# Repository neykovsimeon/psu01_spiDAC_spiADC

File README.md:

# PIC18F2525 with with character 20x4 LCD display

----
## Linear Lab Power Suuply project on PIC18F2525
> IDE MPLAB X IDE 5.05
> Compiler XC8 v2.00

> Use of legacy Microchip's peripheral libraries "plib"  with remarks:

- as for LCD -> changed ports assignments, means the libraries have to be re-located as follows:
  - header file "xlcd.h" moved and included as a local project's  header files, modified respectively
  - source files moved and included as a local project's files , so they are being recompiled

- plib concept used also for spi communications 
  - My git repo for plib archive (while I was still able to find them on Microchip's website):
[plib](https://github.com/neykovsimeon/pic18_plib_legacy.git) 

 - Very helpful "Getting started" tutorial for MPLAB X IDE and XC8:
 [Refrence - YouTube channel StudentCompanion](https://www.youtube.com/watch?v=mUofSucHx_E&list=PL3lfkED2i6JcJH-OETxsI43e8M-7eLeL-)

> use of Universal Programmer MiniPro TL866A. Fuses config comes directly with hex file as per #pragma config statements in respective header file

----
## Scope of this Project
1. Create a bunch of re-usable C functions to utilize 20x4 character display and menu interface
 - [Reference - YouTube channel projectsHigaski, LCD menu tutorial for microcontrollers](https://www.youtube.com/watch?v=PFzNBtnfJ6Y&list=PLfGDzGG5F5eYNBkXs0tTdXqLB3KE5CFgx)
 
2. Use of Microchip's 12bit spi DAC MCP4921 as a set output voltage command interface for the unit

3. Use of Microchip's 12bit spi ADC MCP3208 as for output Voltmener and  Ampermeter

4. Dedicated and re-usable menu structure, easy to handle:
 - menu item selector
 - events handlers ("up", "down", "enter") based on pushbuttons or / and rotary encoder with switch
 - specified function might be called by any of the events handlers (but it is considered event "enter" is the logical way of use)

5. As for fun-trial -> control LCD display's contrast and lightenning via digital potentiometer MCP42010 and PWM on a timer 555
 - [Reference - YouTube EEVblog #392](https://www.youtube.com/watch?v=OXsu29K_Ap4&t=943s)

6. Tracking pre-regulator based on LM2576T-ADJ. Note MCU has no function on this part.
 - [Reference - YouTube EEVblog #260](https://www.youtube.com/watch?v=iTxKCQYMHbY)

7. Output voltage range: 0-15V, (supposed to be 6* Vset, Vset is DAC command voltage at 2.5V Reference voltage with TL431)

8. Output current limit/protection functionality, low side current sense concept used, max current possible (from firmware perspective, in terms of the DAC range) 2.5A.
 - Actual max current would depends of the output power transistors used, heat-sink applied, and the capability of the input voltage source.
   - In my trials I used an laptop power adapter, 20V, 3A.  
   
9. Added  spi serial to parallel I/O expander MCP23S08 together with I/O buffer UDN2595 for higher sink current capability
 - used as an output expander in this project
 - used to control relays and LEDs respectively
 - relays used in a perspective to introduce:
   - PSU output ON/OFF (connect / disconnect) functionality
   - PSU output configured in 2 wire or 4 wite (force / sense concept)
 - added functions 'relDriver_memSet()' , 'relDriver_relSet()'
 - disregarded pushbuttons functionality linked to menu browsing and implemented pushbuttons functions to drive relays respectively
 - 2-wire/4-wire switching not allowed when output is connected (ON)
 - if output change from OFF to ON while 4 wire config - display warning message to make physical connections - wait to press OK to continue!

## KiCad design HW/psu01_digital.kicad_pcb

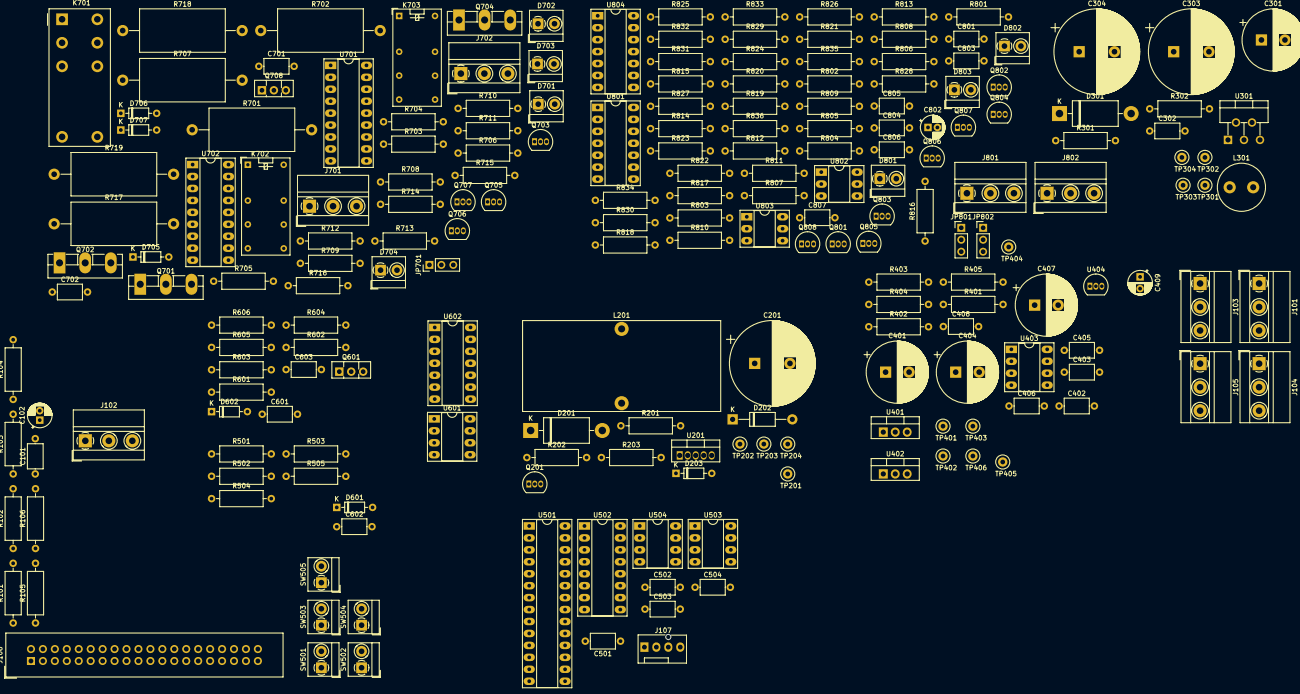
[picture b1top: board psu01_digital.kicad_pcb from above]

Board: 2 copper layers, 204 parts (0 on the bottom side), 139 nets, no tracks yet.

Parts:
C101, C302, C402, C403, C405, C406, C408, C501, C502, C503, C504, C601, C602, C701, C702, C801, C803, C805, C807: 100n; C_Axial_L5.1mm_D3.1mm_P7.50mm_Horizontal
C102: 1uF; CP_Radial_D5.0mm_P2.00mm
C201: 1000uF/63V; CP_Radial_D18.0mm_P7.50mm
C301, C401, C404, C407: 470uF; CP_Radial_D13.0mm_P5.00mm
C303, C304: 2200uF; CP_Radial_D18.0mm_P7.50mm
C409: 1uF; CP_Radial_D5.0mm_P2.50mm
C603: 10n; C_Axial_L5.1mm_D3.1mm_P7.50mm_Horizontal
C802: 10uF; CP_Radial_D5.0mm_P2.00mm
C804, C806: 2.2n; C_Axial_L5.1mm_D3.1mm_P7.50mm_Horizontal
D201, D301: 1N5822; D_DO-201AD_P15.24mm_Horizontal
D202: BZX85C2V7; D_DO-41_SOD81_P12.70mm_Horizontal
D203, D601, D602, D705, D706, D707: 1N4148; D_DO-35_SOD27_P7.62mm_Horizontal
D701, D702: 4wire; TerminalBlock_MetzConnect_Type059_RT06302HBWC_1x02_P3.50mm_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
D703: 2wire; TerminalBlock_MetzConnect_Type059_RT06302HBWC_1x02_P3.50mm_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
D704: Out_OnOff; TerminalBlock_MetzConnect_Type059_RT06302HBWC_1x02_P3.50mm_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
D801: V_REG; TerminalBlock_MetzConnect_Type059_RT06302HBWC_1x02_P3.50mm_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
D802: ALARM; TerminalBlock_MetzConnect_Type059_RT06302HBWC_1x02_P3.50mm_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
D803: I_REG; TerminalBlock_MetzConnect_Type059_RT06302HBWC_1x02_P3.50mm_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
J101: Analog Amper; TerminalBlock_MetzConnect_Type011_RT05503HBWC_1x03_P5.00mm_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
J102: Input_19V; TerminalBlock_MetzConnect_Type011_RT05503HBWC_1x03_P5.00mm_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
J103: FS+; TerminalBlock_MetzConnect_Type011_RT05503HBWC_1x03_P5.00mm_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
J104: Analog Volt; TerminalBlock_MetzConnect_Type011_RT05503HBWC_1x03_P5.00mm_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
J105: FS-; TerminalBlock_MetzConnect_Type011_RT05503HBWC_1x03_P5.00mm_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
J106: ui_iterface; IDC-Header_2x20_P2.54mm_Vertical
J107: BB-CH340T; FanPinHeader_1x04_P2.54mm_Vertical
J701, J702: Screw_Terminal_01x03; TerminalBlock_MetzConnect_Type011_RT05503HBWC_1x03_P5.00mm_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
J801: U_POT_option; TerminalBlock_MetzConnect_Type011_RT05503HBWC_1x03_P5.00mm_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
J802: I_POT_option; TerminalBlock_MetzConnect_Type011_RT05503HBWC_1x03_P5.00mm_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
JP701: Sel_Force_Sense; PinHeader_1x03_P2.54mm_Vertical
JP801: U_POT_option; PinHeader_1x03_P2.54mm_Vertical
JP802: I_POT_option; PinHeader_1x03_P2.54mm_Vertical
K701: Omron_G2RL-2-5VDC; Relay_DPDT_Fujitsu_FTR-F1C
K702, K703: Fujutsu_RY5W-K; Relay_DPDT_Omron_G5V-2
L201: CL100uH_RBQE; L_Toroid_Vertical_L41.9mm_W19.1mm_P15.80mm_Vishay_TJ7
L301: CL33uH_CW8A; L_Radial_D10.0mm_P5.00mm_Fastron_07M
Q201, Q705, Q706: BC557; TO-92_Inline
Q601: BD140; TO-126-3_Vertical
Q701, Q702, Q704: 2SD1047; TO-3PB-3_Vertical
Q703, Q707: BC546; TO-92_Inline
Q708: BD139; TO-126-3_Vertical
Q801, Q802, Q803, Q804, Q805, Q806, Q807, Q808: BC547; TO-92_Inline
R101, R102, R103, R201, R202, R401, R403, R404, R405, R501, R502, R503, R504, R505, R706, R801, R802, R803, R805, R806, R807, R811, R812, R816, R817, R818, R819, R820, R821, R822, R824, R825, R826, R827, R829, R830, R833, R834, R836: 10k; R_Axial_DIN0309_L9.0mm_D3.2mm_P12.70mm_Horizontal
R104, R105, R106: 1meg; R_Axial_DIN0309_L9.0mm_D3.2mm_P12.70mm_Horizontal
R203: 890; R_Axial_DIN0309_L9.0mm_D3.2mm_P12.70mm_Horizontal
R301: 3.2k; R_Axial_DIN0309_L9.0mm_D3.2mm_P12.70mm_Horizontal
R302: 39k; R_Axial_DIN0309_L9.0mm_D3.2mm_P12.70mm_Horizontal
R402, R708, R710: 270; R_Axial_DIN0309_L9.0mm_D3.2mm_P12.70mm_Horizontal
R601: 120k; R_Axial_DIN0309_L9.0mm_D3.2mm_P12.70mm_Horizontal
R602, R605, R606: 1k; R_Axial_DIN0309_L9.0mm_D3.2mm_P12.70mm_Horizontal
R603: 470; R_Axial_DIN0309_L9.0mm_D3.2mm_P12.70mm_Horizontal
R604: 51; R_Axial_DIN0309_L9.0mm_D3.2mm_P12.70mm_Horizontal
R701, R702, R707: 0.56/5W; R_Axial_DIN0918_L18.0mm_D9.0mm_P25.40mm_Horizontal
R703: 120; R_Axial_DIN0309_L9.0mm_D3.2mm_P12.70mm_Horizontal
R704, R705, R804, R808, R809, R813, R814, R823: 220; R_Axial_DIN0309_L9.0mm_D3.2mm_P12.70mm_Horizontal
R709: 3.7k; R_Axial_DIN0309_L9.0mm_D3.2mm_P12.70mm_Horizontal
R711: 1.5k; R_Axial_DIN0309_L9.0mm_D3.2mm_P12.70mm_Horizontal
R712: 91; R_Axial_DIN0309_L9.0mm_D3.2mm_P12.70mm_Horizontal
R713, R714: 100k; R_Axial_DIN0309_L9.0mm_D3.2mm_P12.70mm_Horizontal
R715, R716, R832, R835: 20k; R_Axial_DIN0309_L9.0mm_D3.2mm_P12.70mm_Horizontal
R717, R718, R719: 1ohm/5W; R_Axial_DIN0918_L18.0mm_D9.0mm_P25.40mm_Horizontal
R810, R828: 100; R_Axial_DIN0309_L9.0mm_D3.2mm_P12.70mm_Horizontal
R815, R831: 420; R_Axial_DIN0309_L9.0mm_D3.2mm_P12.70mm_Horizontal
SW501: ROTARY_SW; TerminalBlock_MetzConnect_Type059_RT06302HBWC_1x02_P3.50mm_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
SW502: ROTARY_CK; TerminalBlock_MetzConnect_Type059_RT06302HBWC_1x02_P3.50mm_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
SW503: ROTARY_DA; TerminalBlock_MetzConnect_Type059_RT06302HBWC_1x02_P3.50mm_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
SW504: BTN_2WIRE_4WIRE; TerminalBlock_MetzConnect_Type059_RT06302HBWC_1x02_P3.50mm_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
SW505: BTN_OUT_ONOFF; TerminalBlock_MetzConnect_Type059_RT06302HBWC_1x02_P3.50mm_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
TP201: INPUT_19V; TestPoint_Loop_D2.50mm_Drill1.0mm
TP202, TP302: SW_OUT; TestPoint_Loop_D2.50mm_Drill1.0mm
TP203: Tracking_OUT; TestPoint_Loop_D2.50mm_Drill1.0mm
TP204: GND; TestPoint_Loop_D2.50mm_Drill1.0mm
TP301, TP401: Vin_19V; TestPoint_Loop_D2.50mm_Drill1.0mm
TP303: Vout_5V; TestPoint_Loop_D2.50mm_Drill1.0mm
TP304: V_FB; TestPoint_Loop_D2.50mm_Drill1.0mm
TP402: 12V_ANA; TestPoint_Loop_D2.50mm_Drill1.0mm
TP403: 5V_ANA; TestPoint_Loop_D2.50mm_Drill1.0mm
TP404: Vref_2v5; TestPoint_Loop_D2.50mm_Drill1.0mm
TP405: Vref_DAC; TestPoint_Loop_D2.50mm_Drill1.0mm
TP406: Vref_ADC; TestPoint_Loop_D2.50mm_Drill1.0mm
U201: LM2576T-ADJ; TO-220-5_Vertical
U301: MC33167TV; TO-220-5_P3.4x3.7mm_StaggerOdd_Lead3.8mm_Vertical
U401: L7812; TO-220-3_Vertical
U402: L7805; TO-220-3_Vertical
U403: LM358; DIP-8_W7.62mm_Socket_LongPads
U404: TL431LP; TO-92_Inline
U501: PIC18F2525-I_SP; DIP-28_W7.62mm_Socket_LongPads
U502: MCP3208; DIP-16_W7.62mm_Socket_LongPads
U503, U504: MCP4921-EP; DIP-8_W7.62mm_Socket_LongPads
U601: LMC555xN; DIP-8_W7.62mm_Socket_LongPads
U602: MCP42010; DIP-14_W7.62mm_Socket_LongPads
U701: MCP23S08-E_P; DIP-18_W7.62mm_Socket_LongPads
U702: UDN2595A; DIP-18_W7.62mm_Socket_LongPads
U801, U804: LM324; DIP-14_W7.62mm_Socket_LongPads
U802, U803: H11D1; DIP-6_W7.62mm_Socket_LongPads

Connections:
+12V: C403.1, C404.1, C405.1, C408.1, C801.2, C807.2, TP402.1, U401.3, U402.1, U403.8, U801.4, U804.4
/I_MEAS: R825.2, U502.2, U804.8
/LCD_D4: J106.11, U501.21
/LCD_D5: J106.13, U501.22
/LCD_D6: J106.15, U501.23
/LCD_E: J106.9, U501.12
/LCD_LED_A: J106.19, R604.1
/LCD_RS: J106.5, U501.11
/LCD_RW: J106.7, U501.13
/LCD_Vo: J106.3, U602.9
/LC_D7_BUSY: J106.17, U501.24
/LED_ALARM: D802.1, J106.28, R809.2
/LED_I_REG: D803.1, J106.27, R823.2
/LED_V_REG: D801.1, J106.29, R804.2
/ROTARY_CK: J106.35, R502.2, SW502.1, U501.28
/ROTARY_DA: J106.37, R503.2, SW503.1, U501.6
/ROTARY_SW: J106.39, R501.2, SW501.1, U501.4
/SPI_SCK: R101.2, R104.1, U501.14, U502.13, U503.3, U504.3, U602.2, U701.1
/SPI_SDI: R102.2, R105.1, U501.15, U502.12
/SPI_SDO: R103.2, R106.1, U501.16, U502.11, U503.4, U504.4, U602.3, U701.2
/UART_RX: J107.2, U501.18
/UART_TX: J107.3, U501.17
/U_MEAS: R826.2, U502.1, U804.14
/Vout_Force+: J101.1, K701.8
/Vout_Force-: J105.3, K701.1
/Vsense+: J103.3, J104.1, K702.8
/Vsense-: J104.3, J105.1, K702.9
/ana_reg/Vref_DAC: J801.1, J802.1, R401.1, TP405.1, U403.1, U503.6, U504.6
/ana_reg/drv_ctrl: C802.1, Q706.1, Q708.3, R710.1, U802.1, U803.1
/ana_reg/i_fb_low: K701.2, K703.11, R716.2, R717.1, R718.1, R719.1, R832.2, R834.2
/ana_reg/i_fb_low_buff: R829.1, R833.2, R835.2, U804.7
/ana_reg/i_reg_active: R818.1, R822.2, R823.1, U803.5
/ana_reg/u_fb: R714.2, R715.1, R805.1
/ana_reg/u_fb_buff: R807.1, R812.2, R830.1, U801.1
/ana_reg/u_fb_sense: K703.13, R715.2, R716.1, R821.1
/ana_reg/u_reg_active: R804.1, R817.1, R820.2, U802.5
/bnt_4wire: J106.33, R504.2, SW504.1, U501.1
/btn_onoff: J106.31, R505.2, SW505.1, U501.7
/led_2wire: D703.1, J106.23, R704.1
/led_out_onoff: D704.1, J106.21, R705.1
/leds_4wire: D702.1, J106.25, R703.1
/mcu_adi/I_cmd_DAC: JP802.1, U504.8
/mcu_adi/SPI_CS_ADC: U501.5, U502.10
/mcu_adi/SPI_~CS~_DAC_I: U501.9, U504.2
/mcu_adi/SPI_~CS~_DAC_U: U501.25, U503.2
/mcu_adi/U_cmd_DAC: JP801.1, U503.8
/mcu_adi/Vref_ADC: R405.1, TP406.1, U403.7, U502.15
/pwr_drv_out/Out_2wire_4wire: D707.2, K703.16, R703.2, R706.2, U702.16
/pwr_drv_out/Out_OnOff_Force: D706.2, JP701.1, K701.5, R705.2, U702.18
/pwr_drv_out/Out_OnOff_Sense: JP701.3, U702.17
/pwr_drv_out/Rel_2Wire4Wire: U701.12, U702.3
/pwr_drv_out/Rel_ONOFFF: U701.10, U702.1
/pwr_drv_out/Rel_ONOFFS: U701.11, U702.2
/pwr_tracking_preReg/Tracking_FB: K701.7, K703.6, R202.1, R701.1, R702.1, R707.1, R708.1, R713.1
/~ALARM: Q804.1, R809.1, U501.26
/~CS~_DISPL: U501.27, U602.1
/~CS~_IOEXP: U501.2, U701.7
GND: C101.2, C102.2, C201.2, C301.2, C303.2, C304.2, C401.2, C402.2, C403.2, C404.2, C405.2, C406.2, C407.2, C408.2, C409.2, C501.1, C502.2, C503.2, C504.2, C601.2, C602.2, C603.1, C701.2, C702.1, C801.1, C802.2, C807.1, D201.2, D301.2, J102.3, J106.2, J106.4, J106.6, J106.8, J106.10, J106.12, J106.14, J106.16, J106.18, J106.20, J106.22, J106.24, J106.26, J106.30, J106.32, J106.34, J106.36, J106.38, J106.40, J107.4, J801.3, J802.3, Q703.3, Q801.3, Q804.3, Q805.3, Q807.3, Q808.3, R104.2, R105.2, R106.2, R203.2, R711.2, R712.2, R717.2, R718.2, R719.2, R802.2, R815.1, R831.2, R836.2, SW501.2, SW502.2, SW503.2, SW504.2, SW505.2, TP204.1, U201.3, U201.5, U301.3, U401.2, U402.2, U403.4, U404.2, U501.8, U501.19, U502.9, U502.14, U503.5, U503.7, U504.5, U504.7, U601.1, U602.4, U602.10, U701.4, U701.5, U701.9, U702.10, U801.11, U802.4, U803.4, U804.11
unnamed: C302.1, U301.5
unnamed: C302.2, R302.2
unnamed: C409.1, R402.2, R403.2, R404.2, TP404.1, U404.1, U404.3
unnamed: C603.2, U601.5
unnamed: C803.1, R806.2, U801.13
unnamed: C803.2, R810.2, U801.14
unnamed: C804.1, Q801.1, U802.2
unnamed: C804.2, Q801.2, R810.1, R815.2
unnamed: C805.1, R828.1, U804.1
unnamed: C805.2, R827.2, U804.2
unnamed: C806.1, Q808.1, U803.2
unnamed: C806.2, Q808.2, R828.2, R831.1
unnamed: D201.1, L201.1, TP202.1, U201.2
unnamed: D202.2, Q201.3
unnamed: D203.2, Q201.2, R202.2
unnamed: D301.1, L301.1, TP302.1, U301.2
unnamed: D601.1, D602.2, R602.1, U601.7
unnamed: D601.2, U602.5
unnamed: D602.1, U602.7
unnamed: D701.1, D702.2
unnamed: D705.2, JP701.2, K702.16
unnamed: J101.3, J103.1
unnamed: J701.1, Q701.3, R701.2
unnamed: J701.2, Q702.3, R702.2
unnamed: J701.3, Q704.3, R707.2
unnamed: J702.3, Q701.1, Q702.1, Q704.1, Q708.1, R708.2
unnamed: J801.2, JP801.3
unnamed: J802.2, JP802.3
unnamed: JP801.2, R806.1
unnamed: JP802.2, R827.1
unnamed: K701.3, K702.13, K703.9
unnamed: K701.6, K702.4, K703.8
unnamed: K703.4, R713.2, R714.1
unnamed: Q201.1, R201.2, R203.1, U201.4
unnamed: Q601.2, R604.2
unnamed: Q601.3, R603.1
unnamed: Q703.1, R704.2
unnamed: Q703.2, R706.1
unnamed: Q705.1, Q705.2, Q706.2, Q707.1
unnamed: Q707.2, R709.2, R711.1
unnamed: Q707.3, R712.1
unnamed: Q802.1, Q803.1, R808.1, R811.2
unnamed: Q802.2, R817.2
unnamed: Q802.3, Q803.3, Q805.1, R814.1
unnamed: Q803.2, R818.2
unnamed: Q804.2, R811.1
unnamed: Q805.2, R816.1
unnamed: Q806.1, R813.1, R816.2
unnamed: Q806.2, R820.1
unnamed: Q806.3, Q807.1
unnamed: Q807.2, R822.1
unnamed: R301.2, R302.1, TP304.1, U301.1
unnamed: R401.2, U403.2
unnamed: R403.1, U403.3
unnamed: R404.1, U403.5
unnamed: R405.2, U403.6
unnamed: R601.1, U602.8
unnamed: R603.2, U601.3
unnamed: R605.1, U602.11
unnamed: R606.1, U602.12
unnamed: R801.1, U801.9
unnamed: R801.2, R803.1, U801.8
unnamed: R802.1, R803.2, U801.3
unnamed: R805.2, U801.10
unnamed: R807.2, R819.2, U801.2
unnamed: R812.1, U801.12
unnamed: R819.1, R824.2, U801.7
unnamed: R821.2, U801.5
unnamed: R824.1, U801.6
unnamed: R825.1, U804.9
unnamed: R826.1, U804.13
unnamed: R829.2, U804.10
unnamed: R830.2, U804.12
unnamed: R832.1, R834.1, U804.5
unnamed: R833.1, U804.3
unnamed: R835.1, R836.1, U804.6
unnamed: U601.2, U601.6, U602.6
VDD: C101.1, C102.1, C303.1, C304.1, C501.2, C601.1, C602.1, C701.1, C702.2, D701.2, D703.2, D704.2, D705.1, D706.1, D707.1, D801.2, D802.2, D803.2, J106.1, J107.1, K701.4, K702.1, K703.1, L301.2, Q601.1, R101.1, R102.1, R103.1, R301.1, R501.1, R502.1, R503.1, R504.1, R505.1, R601.2, R602.2, R605.2, R606.2, R808.2, R813.2, R814.2, TP303.1, U501.20, U601.4, U601.8, U602.14, U701.6, U701.18, U702.9
VDDA: C406.1, C407.1, C502.1, C503.1, C504.1, R402.1, R709.1, TP403.1, U402.3, U502.16, U503.1, U504.1
VS: C301.1, C401.1, C402.1, J102.1, TP201.1, TP301.1, TP401.1, U201.1, U301.4, U401.1
Vdrive: C201.1, D202.1, D203.1, J702.1, L201.2, Q701.2, Q702.2, Q704.2, Q705.3, Q706.3, Q708.2, R201.1, R710.2, TP203.1

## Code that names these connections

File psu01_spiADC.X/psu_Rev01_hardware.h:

#ifndef __HARDWARE
#define __HARDWARE

//#include <stdlib.h>
//#include <delays.h>
//#include "xlcd.h"

// user HW definitions
#define Button_2Wite4Wite       RE3                     // ->> check it on your bread board !!!! digital input button, active low -> select contrast or brightness control
#define SPI_CS_IOUT             LATAbits.LATA7          // digital output CS dac i set  
#define ROTARY_DA               PORTAbits.RA4           // digital input button, active low -> contrast / brightness decrease
#define SPI_CS_UOUT             LATBbits.LATB4          // digital output CS dac v set
#define DISPLAY_SET_UP          PORTAbits.RA5           // digital input button, active low -> contrast / brightness increase
#define DISPLAY_SET_DOWN        PORTAbits.RA6           // digital input button, active low -> contrast / brightness decrease
#define ROTARY_SW               PORTAbits.RA2           // digital input button, active low -> output settings menu
#define SPI_CS_DISPLAY          LATBbits.LATB6          // digital output, CS digital pot for displ contrast and brightness
#define ROTARY_CK               PORTBbits.RB7           // digital input button, active low -> contrast / brightness decrease
#define IPROT                   PORTBbits.RB5           // digital input, interrup on change -> detect current regulator comparator
#define RxD                     LATCbits.LATC7          // rs232 input, 
#define TxD                     LATCbits.LATC6          // rs232 output, 
#define SPI_CS_ADC              LATAbits.LATA3          // digital output CS spiADC
#define SPI_CS_IOEXT            LATAbits.LATA0          // digital output CS MCp23S08 io expander
#define Button_ONOFF            PORTAbits.RA5           // digital input button, active low -> contrast / brightness increase
#define DISPLAY_SET_MODE_SELECT PORTAbits.RA6           // ->> check it on your bread board; digital input button, active low -> contrast / brightness decrease

void init_GPIO_DIR (void);

#endif   /*    HARDWARE    */

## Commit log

2019-07-20 Initial commit, PCU_Rev001, spi dac, spi adc, mcu menu, rotary encoder
2019-07-20 Added README
2019-07-20 Added LTSpice reference concept design
2019-08-11 to add relDriver MCP23S08
2019-08-18 Rev004 - added MCP23S08 spi driver, added output ON/OFF and 2 wire / 4 wire configs
2020-02-23 Initial HW
2020-02-23 After merge relDriver to master
